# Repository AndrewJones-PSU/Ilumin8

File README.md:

Ilumin8 (pre-release)
=====================

Version: Development (unreleased)
---------------------------------

Ilumin8 is a program for the Arduino Due that acts as an interface for LED strips using NeoPixel/WS281X LED drivers. Our goal with this program is to provide a controller that is easy to use for end users who may not have a lot of technological knowledge/eperience, yet efficient enough to run elaborate and complex lighting effects, such as syncing lighting effects to music played from a computer. 

Please note that Ilumin8 is currently still in early development, and some parts of the program may be broken and not work as intended, or are currently unimplemented.

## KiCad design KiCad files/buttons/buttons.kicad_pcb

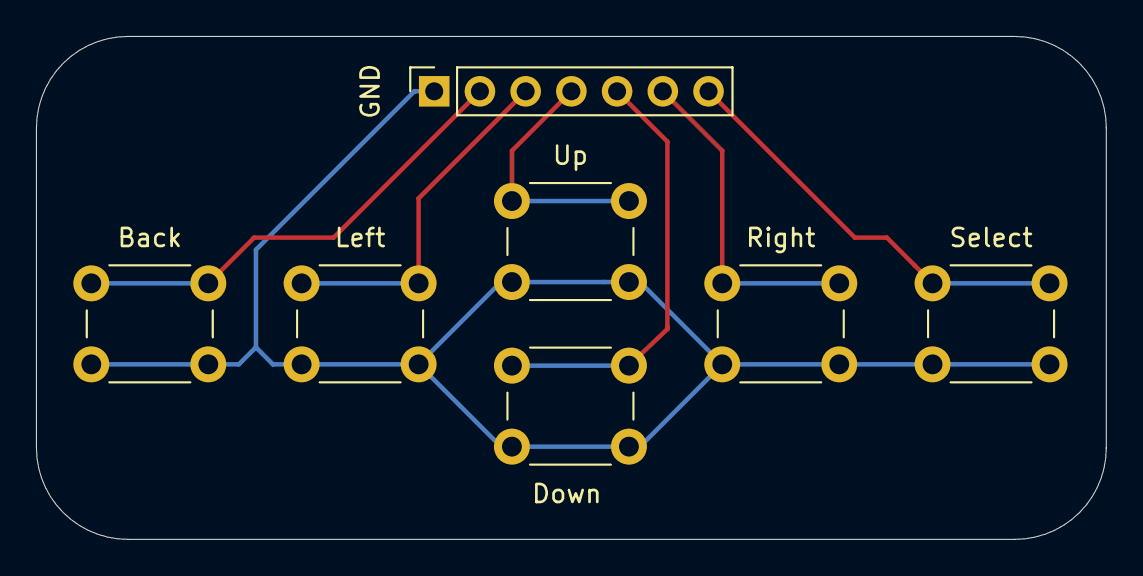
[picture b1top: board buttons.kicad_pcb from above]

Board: 2 copper layers, 59.4 x 27.9 mm, 7 parts (0 on the bottom side), 7 nets.

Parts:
Back: SW_Push; SW_PUSH_6mm
Down: SW_Push; SW_PUSH_6mm
GND: Conn_01x06; PinSocket_1x07_P2.54mm_Vertical
Left: SW_Push; SW_PUSH_6mm
Right: SW_Push; SW_PUSH_6mm
Select: SW_Push; SW_PUSH_6mm
Up: SW_Push; SW_PUSH_6mm

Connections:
unnamed: Back.1, GND.2
unnamed: Back.2, Down.2, GND.1, Left.2, Right.2, Select.2, Up.2
unnamed: Down.1, GND.5
unnamed: GND.3, Left.1
unnamed: GND.6, Right.1
unnamed: GND.7, Select.1
unnamed: GND.4, Up.1

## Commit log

2020-05-31 Added KiCad files for button PCB
2020-07-04 Reworked a bunch of stuff, treat this as an initial commit.
2020-07-04 Initial Commit of Serial Control Panel
2020-07-10 Added interface program for UE4 to interface with (The UE4duino plugin won't send serial data if the program freezes, dedicating serial interfacing to a seperate program and then having the 2 program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
2020-07-19 Added comments + prompts for port number and interface. Also changed baudrate to 256000, will revert back to 115200 if 256K proves to be unreliable
2020-07-26 Implemented non-blocking console input, as well as command line parameter checking and different cin rules for when running as an integrated process/subprocess
2020-07-26 implemented changing brightness through FastLED over serial (default brightness is hard-coded to 40)
2020-07-26 updated some outdated comments in commandList, as well as reorganized the cmds namespace. Also removed obsolete definitions.
2020-07-26 changed default baudrate from 256K to 250K
2020-07-27 Changed Lightshows.h from a namespace to a class, as well as implemented a struct for storing options that can be easily added onto in the future.
2020-07-27 changed main loop to use sleep_for function instead of an empty while-loop
2020-07-27 Changed WhiteLights lightshow to SolidColor, added implementation for sending lightshow-specific options over serial as well as a basic implementation of one option (specifically changing the color o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
2020-08-10 Added an optional feature where a user can attach a push button that can toggle the lightstrips on and off.
2020-08-10 added a call to LEDS.show() after the toggle on off button was pressed down, allowing the lightstrips to toggle on and off without requiring serial input to call LEDS.show()
2020-08-11 lightstrips can now be toggled on/off over serial and not just through the hardware push-button
2020-08-13 Made rainbow lightshow seamless, also increased gaps in rainbowdrip
2020-08-14 adjusted RainbowDrip initialization to make color drips less blocky in appearence
2020-08-17 added ability for ilumin8 CLI to interpret floats from user command line
2020-08-18 Added LengthBias option for rainbow drip, allowing the length of each drip to be customized over serial
